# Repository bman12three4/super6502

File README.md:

# Super6502

## Overview

Super6502 is a microcomputer system powered by a 65C02 CPU. The goal of this
project is to create a computer system with modern features and the ability to
run modern software on an unmodified 65C02 core. While the project is almost
entirely contained in an FPGA, this rule is enforced by using an off the shelf
CPU.

## Goals

There are a few goals that I have for this project.

The number 1 goal is to create a pre-emptive multitasking operating system with
virtual memory.

I also have a few stretch goals:

1. Connect it to the internet

2. Boot linux (lol)

Along the way, there are a few milestones that I want to reach:

* USB support, including mass storage and peripherals
* HDMI Display output
* Ethernet

## Contributing

While I appreciate feedback, this my own personal project and I will not accept
external contributions.

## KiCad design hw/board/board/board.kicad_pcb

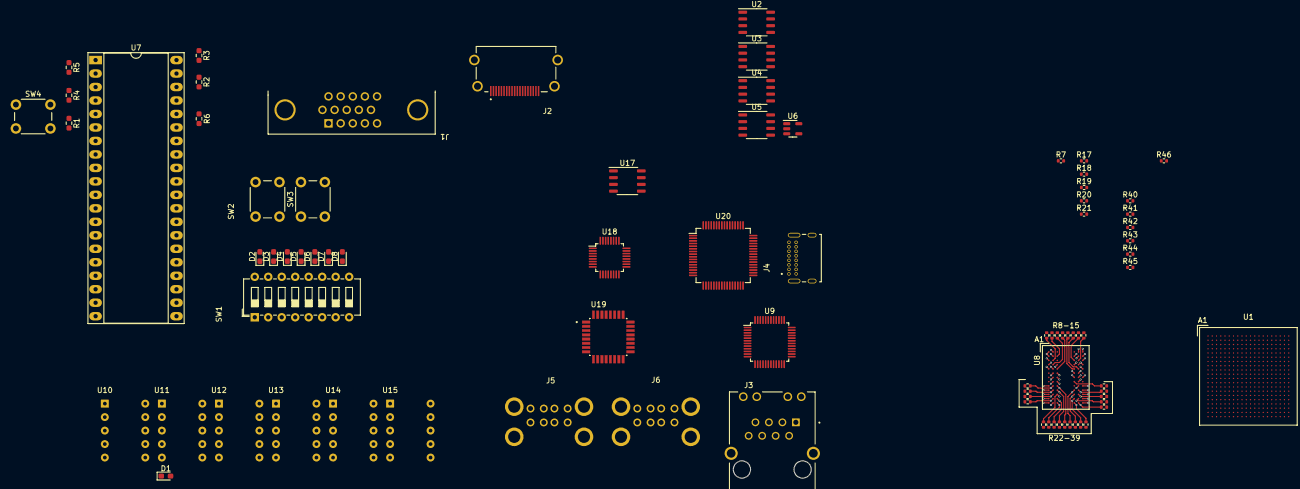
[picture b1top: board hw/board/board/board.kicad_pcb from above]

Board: 6 copper layers, 82 parts (0 on the bottom side), 59 nets.

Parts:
D1, D2, D3, D4, D5, D6, D7, D8: LED; LED_0603_1608Metric_Pad1.05x0.95mm_HandSolder
J1: DB15_Female_HighDensity_MountingHoles; ICD15S13E4GX00LF
J2: 10029449-111RLF; AMPHENOL_10029449-111RLF
J3: SI-50170-F; BEL_SI-50170-F
J4: USB4085-GF-A_REVB; GCT_USB4085-GF-A_REVB
J5, J6: USB_A_Stacked; 0672984091
R1, R2, R3, R4, R5, R6: 10K; R_0603_1608Metric_Pad0.98x0.95mm_HandSolder
R7: 100R; R_0402_1005Metric
R8, R9, R10, R11, R12, R13, R14, R15, R17, R18: 15R; R_0402_1005Metric
R19, R46: 240R; R_0402_1005Metric
R20, R21: 1k; R_0402_1005Metric
R22, R23, R24, R25, R26, R27, R28, R29, R30, R31, R32, R33, R34, R35, R36, R37, R38, R39, R40, R41, R42, R43, R44, R45: 40R; R_0402_1005Metric
SW1: SW_DIP_x08; SW_DIP_SPSTx08_Slide_6.7x21.88mm_W7.62mm_P2.54mm_LowProfile
SW2, SW3, SW4: SW_Push; SW_PUSH_6mm_H5mm
U1: BGA-400_17.0x17.0mm_Layout20x20_P0.8mm
U2, U3, U4, U5, U17: SOP-8_3.9x4.9mm_P1.27mm
U6: TSOT-23-5
U7: W65C02P; DIP-40_W15.24mm_Socket_LongPads
U8: BGA-78_8.0x10.5mm_Layout9x12_P0.8mm
U9: LQFP-48_7x7mm_P0.5mm
U10, U11, U12, U13, U14, U15: LTS-4802B
U18: MAX3421E; LQFP-32_5x5mm_P0.5mm
U19: TUSB2046BVFR; QFP80P900X900X160-32N
U20: FT4232H; LQFP-64_10x10mm_P0.5mm

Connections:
+1V35: R20.1, U1.L7 (VCCIO_DDR), U1.N7 (VCCIO_DDR), U1.P5 (VCCIO_DDR), U1.R2 (VCCIO_DDR), U1.R7 (VCCIO_DDR), U1.W4 (VCCIO_DDR), U8.A2 (VDD), U8.A9 (VDD), U8.B9 (VDDQ), U8.C1 (VDDQ), U8.D7 (VDD), U8.E2 (VDDQ), U8.E9 (VDDQ), U8.G2 (VDD), U8.G8 (VDD), U8.K1 (VDD), U8.K9 (VDD), U8.M1 (VDD), U8.M9 (VDD)
+3V3: R1.1, R2.1, R3.1, R4.1, R5.1, R6.1, U7.8 (VDD)
/cpu/CPU_BE: R6.2, U7.36 (BE)
/cpu/CPU_RDY: R5.2, U7.2 (RDY)
/cpu/~CPU_IRQB: R4.2, U7.4 (~IRQB)
/cpu/~CPU_NMIB: R1.2, SW4.2, U7.6 (~NMIB)
/cpu/~CPU_RESB: R3.2, U7.40 (~RESB)
/ddr/DDR_A0: R22.2, U1.U4 (DDR_A0), U8.K3 (A0)
/ddr/DDR_A1: R23.2, U1.W5 (DDR_A1), U8.L7 (A1)
/ddr/DDR_A2: R24.2, U1.V5 (DDR_A2), U8.L3 (A2)
/ddr/DDR_A3: R25.2, U1.T6 (DDR_A3), U8.K2 (A3)
/ddr/DDR_A4: R26.2, U1.T3 (DDR_A4), U8.L8 (A4)
/ddr/DDR_A5: R27.2, U1.T5 (DDR_A5), U8.L2 (A5)
/ddr/DDR_A6: R28.2, U1.T4 (DDR_A6), U8.M8 (A6)
/ddr/DDR_A7: R29.2, U1.T1 (DDR_A7), U8.M2 (A7)
/ddr/DDR_A8: R30.2, U1.R1 (DDR_A8), U8.N8 (A8)
/ddr/DDR_A9: R31.2, U1.T2 (DDR_A9), U8.M3 (A9)
/ddr/DDR_A10: R32.2, U1.R5 (DDR_A10), U8.H7 (A10/AP)
/ddr/DDR_A11: R33.2, U1.N5 (DDR_A11), U8.M7 (A11)
/ddr/DDR_A12: R34.2, U1.P4 (DDR_A12), U8.K7 (A12/BC#)
/ddr/DDR_A13: R35.2, U1.M6 (DDR_A13), U8.N3 (A13)
/ddr/DDR_A14: R36.2, U1.N4 (DDR_A14), U8.N7 (A14)
/ddr/DDR_BA0: R37.2, U1.K3 (DDR_BA0), U8.J2 (BA0)
/ddr/DDR_BA1: R38.2, U1.K2 (DDR_BA2), U8.K8 (BA1)
/ddr/DDR_BA2: R39.2, U1.K1 (DDR_BA2), U8.J3 (BA2)
/ddr/DDR_CAS#: R42.2, U1.P6 (DDR_CAS_N), U8.G3 (CAS#)
/ddr/DDR_CK: R7.1, U1.R3 (DDR_CK), U8.F7 (CK)
/ddr/DDR_CK#: R7.2, U1.R4 (DDR_CK_N), U8.G7 (CK#)
/ddr/DDR_CKE: R40.2, U1.N6 (DDR_CKE), U8.G9 (CKE)
/ddr/DDR_CS#: R44.2, U1.R6 (DDR_CS_N), U8.H2 (CS#)
/ddr/DDR_DM: R18.1, U1.W1 (DDR_DM0)
/ddr/DDR_DQ0: R8.1, U1.U3 (DDR_DQ0)
/ddr/DDR_DQ1: R9.1, U1.W3 (DDR_DQ1)
/ddr/DDR_DQ2: R10.1, U1.V3 (DDR_DQ2)
/ddr/DDR_DQ3: R11.1, U1.U2 (DDR_DQ3)
/ddr/DDR_DQ4: R12.1, U1.W2 (DDR_DQ4)
/ddr/DDR_DQ5: R13.1, U1.Y3 (DDR_DQ5)
/ddr/DDR_DQ6: R14.1, U1.Y4 (DDR_DQ6)
/ddr/DDR_DQ7: R15.1, U1.Y2 (DDR_DQ7)
/ddr/DDR_DQS#: R17.1, U1.U1 (DDR_DQS_N0)
/ddr/DDR_ODT: R45.2, U1.L6 (DDR_ODT), U8.G1 (ODT)
/ddr/DDR_RAS#: R43.2, U1.M4 (DDR_RAS_N), U8.F3 (RAS#)
/ddr/DDR_RESET#: U1.L4 (DDR_RST_N), U8.N2 (RESET#)
/ddr/DDR_WE#: R41.2, U1.K4 (DDR_WE_N), U8.H3 (WE#)
/ddr/VTT: R20.2, R21.1, R22.1, R23.1, R24.1, R25.1, R26.1, R27.1, R28.1, R29.1, R30.1, R31.1, R32.1, R33.1, R34.1, R35.1, R36.1, R37.1, R38.1, R39.1, R40.1, R41.1, R42.1, R43.1, R44.1, R45.1, U8.E1 (VREFDQ), U8.J8 (VREFCA)
GND: R19.2, R21.2, R46.2, SW4.1, U7.21 (VSS), U8.A1 (VSS), U8.A8 (VSS), U8.B1 (VSS), U8.B2 (VSSQ), U8.B8 (VSSQ), U8.C9 (VSSQ), U8.D1 (VSSQ), U8.D8 (VSS), U8.D9 (VSSQ), U8.F2 (VSS), U8.F8 (VSS), U8.J1 (VSS), U8.J9 (VSS), U8.L1 (VSS), U8.L9 (VSS), U8.N1 (VSS), U8.N9 (VSS)
unnamed: R46.1, U1.Y5 (DDR_ZQ)
unnamed: R2.2, U7.38 (~SOB)
unnamed: R18.2, U8.B7 (DM/TDQS)
unnamed: R8.2, U8.B3 (DQ0)
unnamed: R9.2, U8.C7 (DQ1)
unnamed: R10.2, U8.C2 (DQ2)
unnamed: R11.2, U8.C8 (DQ3)
unnamed: R12.2, U8.E3 (DQ4)
unnamed: R13.2, U8.E8 (DQ5)
unnamed: R14.2, U8.D2 (DQ6)
unnamed: R15.2, U8.E7 (DQ7)
unnamed: R17.2, U8.D3 (DQS#)
unnamed: R19.1, U8.H8 (ZQ)

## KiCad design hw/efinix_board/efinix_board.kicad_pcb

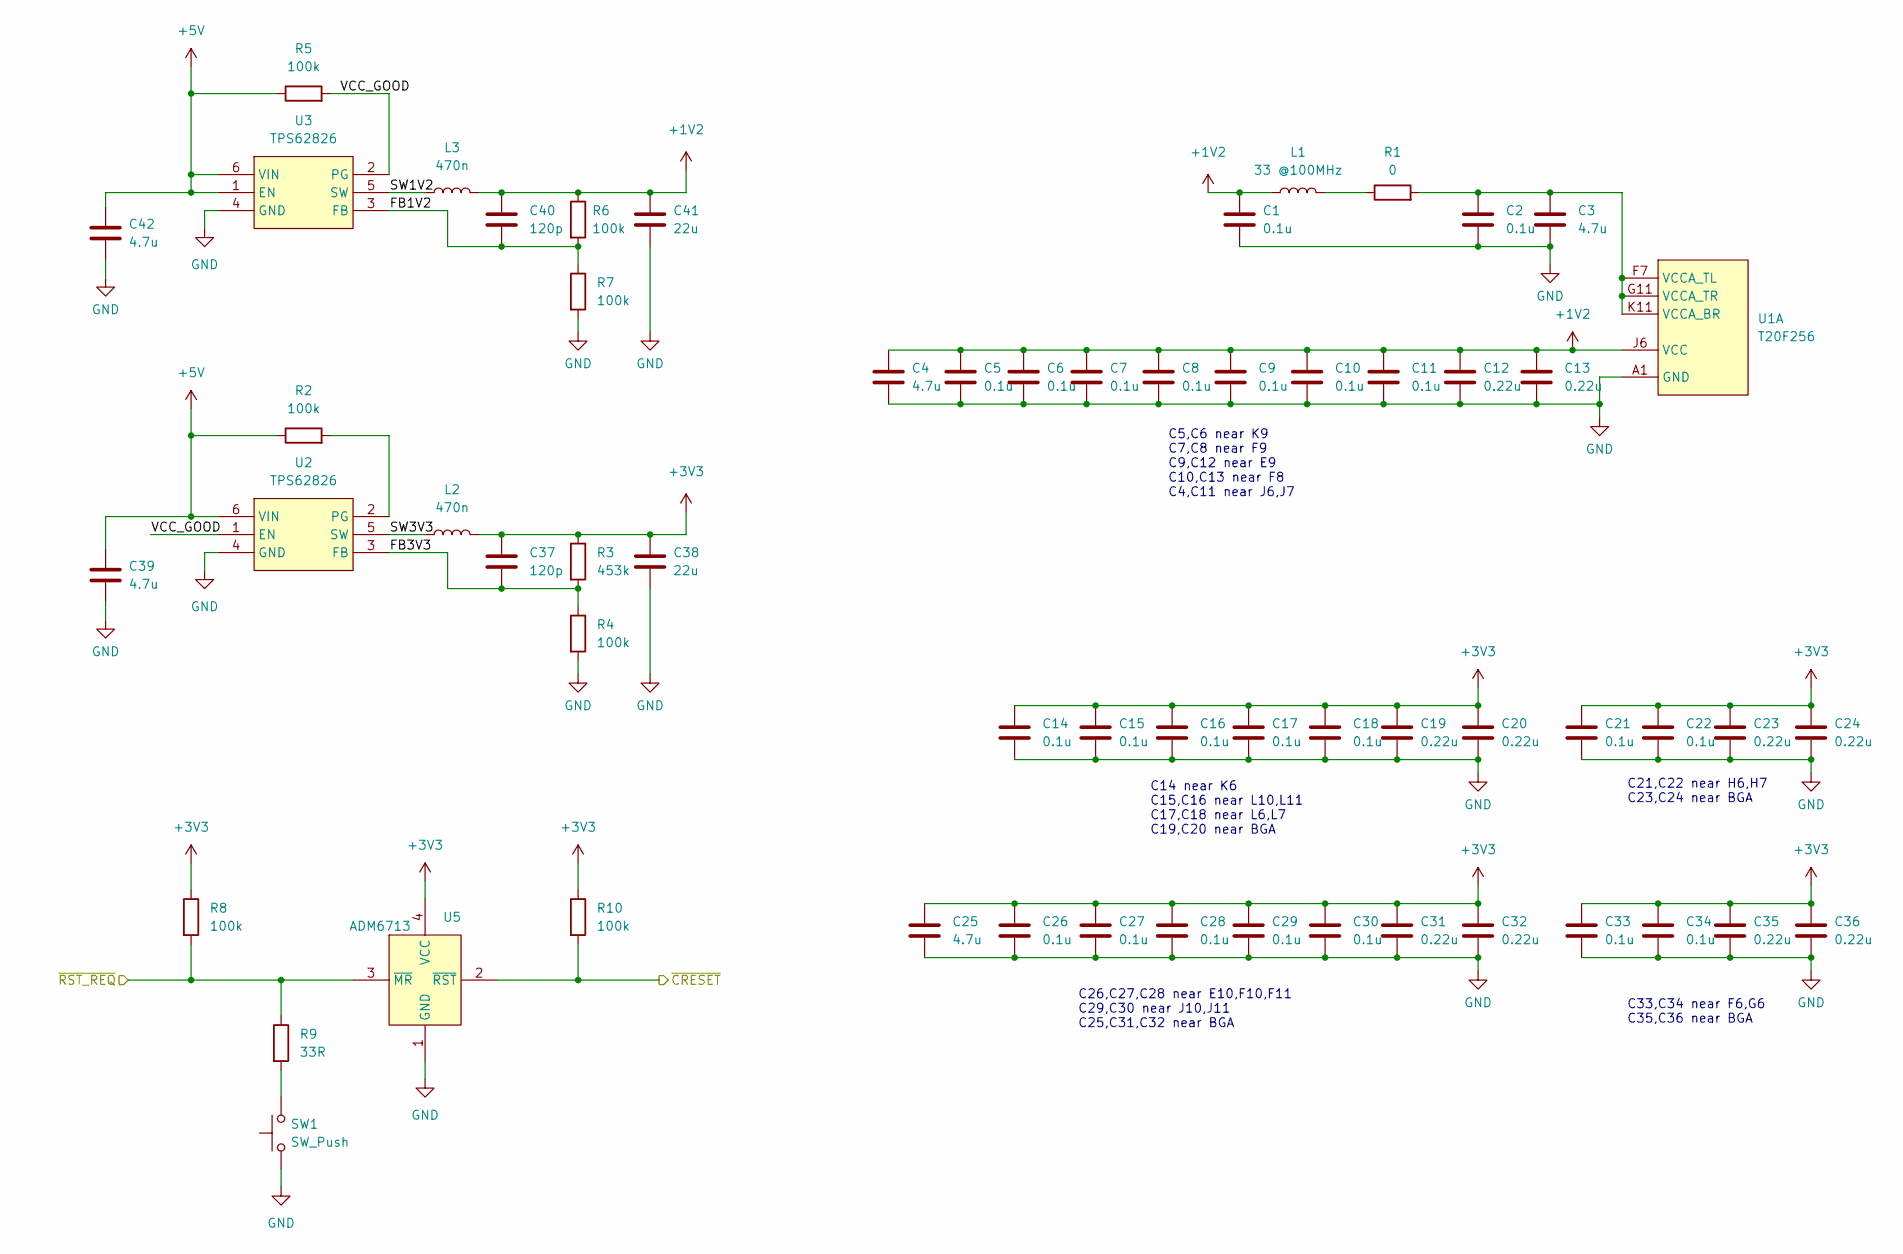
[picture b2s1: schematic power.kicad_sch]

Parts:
C1, C2, C5, C6, C7, C8, C9, C10, C11, C14, C15, C16, C17, C18, C21, C22, C26, C27, C28, C29, C30, C33, C34: 0.1u; C_0201_Small
C3, C4, C25: 4.7u; C_0402_1005Metric
C12, C13, C19, C20, C23, C24, C31, C32, C35, C36: 0.22u; C_0201_Small
C37, C40: 120p; C_0402_1005Metric
C38, C41: 22u; C_0603_1608Metric
C39, C42: 4.7u; C_0603_1608Metric
L1: 33 @100MHz; L_0402_1005Metric
L2, L3: 470n; L_Vishay_IHLP-1212
R1: 0; R_0603_1608Metric
R2, R5: 100k; R_0603_1608Metric
R3: 453k; R_0402_1005Metric
R4, R6, R7, R8, R10: 100k; R_0402_1005Metric
R9: 33R; R_0402_1005Metric
SW1: SW_Push; SW_1825966-1
U1: T20F256; BGA-256_14.0x14.0mm_Layout16x16_P0.8mm_Ball0.45mm_Pad0.32mm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
U2, U3: TPS62826; VFDFN-6
U5: ADM6713; ADM6711TAKSZ-REEL7

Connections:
+1V2: C1.1, C4.1, C5.1, C6.1, C7.1, C8.1, C9.1, C10.1, C11.1, C12.1, C13.1, C40.1, C41.1, L1.1, L3.2, R6.1, U1.E9 (VCC), U1.F8 (VCC), U1.F9 (VCC), U1.J6 (VCC), U1.J7 (VCC), U1.K9 (VCC)
+3V3: C14.1, C15.1, C16.1, C17.1, C18.1, C19.1, C20.1, C21.1, C22.1, C23.1, C24.1, C25.1, C26.1, C27.1, C28.1, C29.1, C30.1, C31.1, C32.1, C33.1, C34.1, C35.1, C36.1, C37.1, C38.1, L2.2, R3.1, R8.1, R10.1, U5.4 (VCC); also elsewhere on the board
+5V: C39.1, C42.1, R2.1, R5.1, U2.6 (VIN), U3.1 (EN), U3.6 (VIN)
/Power/FB1V2: C40.2, R6.2, R7.1, U3.3 (FB)
/Power/FB3V3: C37.2, R3.2, R4.1, U2.3 (FB)
/Power/SW1V2: L3.1, U3.5 (SW)
/Power/SW3V3: L2.1, U2.5 (SW)
/Power/VCC_GOOD: R5.2, U2.1 (EN), U3.2 (PG)
/Power/~CRESET: R10.2, U5.2 (~RST)
/Power/~RST_REQ: R8.2, R9.1, U5.3 (~MR)
GND: C1.2, C2.2, C3.2, C4.2, C5.2, C6.2, C7.2, C8.2, C9.2, C10.2, C11.2, C12.2, C13.2, C14.2, C15.2, C16.2, C17.2, C18.2, C19.2, C20.2, C21.2, C22.2, C23.2, C24.2, C25.2, C26.2, C27.2, C28.2, C29.2, C30.2, C31.2, C32.2, C33.2, C34.2, C35.2, C36.2, C38.2, C39.2, C41.2, C42.2, R4.2, R7.2, SW1.1, U1.A1 (GND), U1.A5 (GND), U1.A12 (GND), U1.A16 (GND), U1.D2 (GND), U1.D15 (GND), U1.G7 (GND), U1.G8 (GND), U1.G9 (GND), U1.G10 (GND), U1.H8 (GND), U1.H9 (GND), U1.H10 (GND), U1.H11 (GND), U1.J1 (GND), U1.J8 (GND), U1.J9 (GND), U1.J16 (GND), U1.K7 (GND), U1.K8 (GND), U1.K10 (GND), U1.L8 (GND), U1.L9 (GND), U1.N2 (GND), U1.N15 (GND), U1.R7 (GND), U1.R10 (GND), U1.T1 (GND), U1.T4 (GND), U1.T13 (GND), U1.T16 (GND), U2.4 (GND), U3.4 (GND), U5.1 (GND); also elsewhere on the board
unnamed: C2.1, C3.1, R1.2, U1.F7 (VCCA_TL), U1.G11 (VCCA_TR), U1.K11 (VCCA_BR)
unnamed: L1.2, R1.1
unnamed: R2.2, U2.2 (PG)
unnamed: R9.2, SW1.2

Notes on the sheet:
C21,C22 near H6,H7 C23,C24 near BGA
C5,C6 near K9 C7,C8 near F9 C9,C12 near E9 C10,C13 near F8 C4,C11 near J6,J7
C33,C34 near F6,G6 C35,C36 near BGA
C26,C27,C28 near E10,F10,F11 C29,C30 near J10,J11 C25,C31,C32 near BGA
C14 near K6 C15,C16 near L10,L11 C17,C18 near L6,L7 C19,C20 near BGA

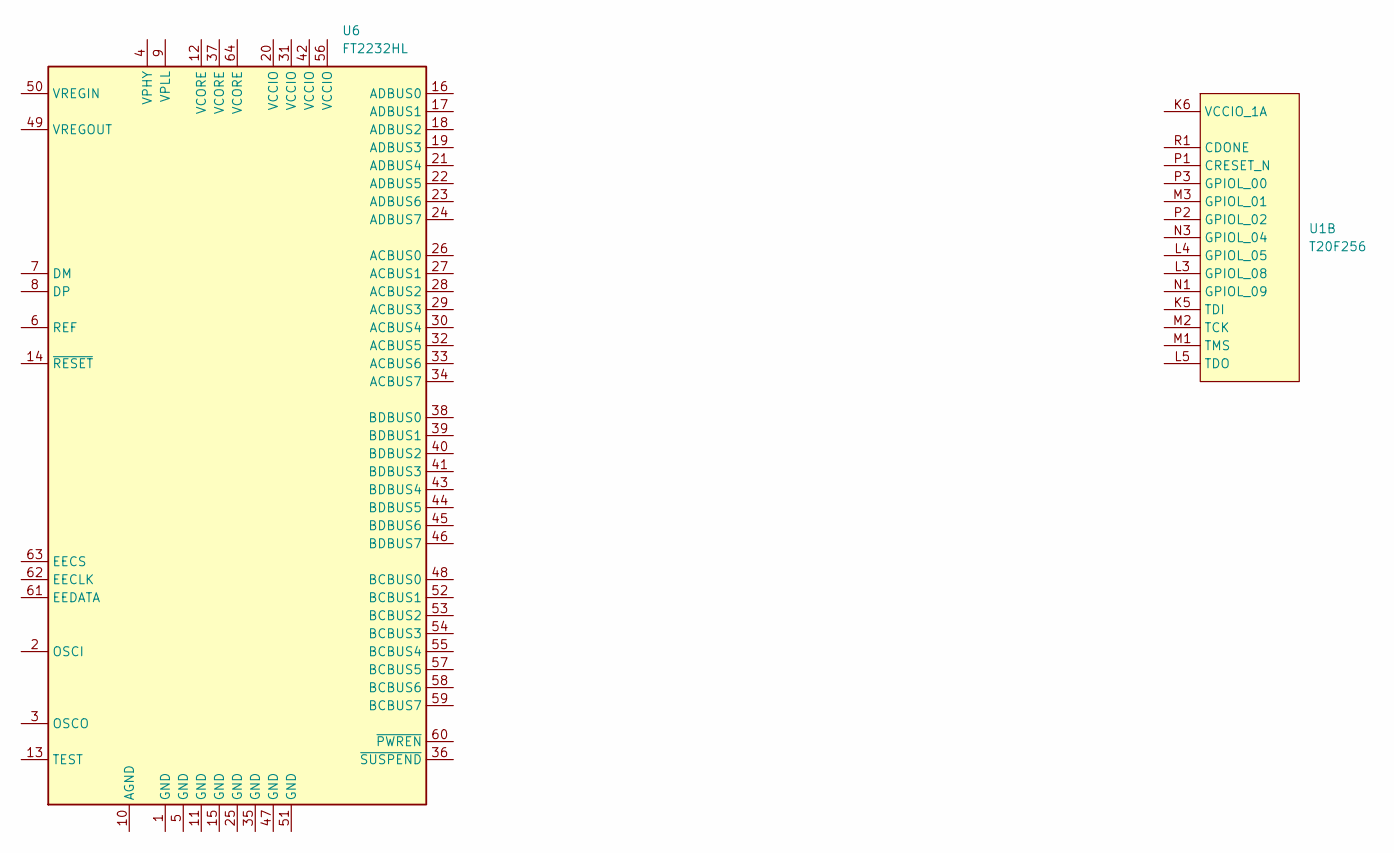
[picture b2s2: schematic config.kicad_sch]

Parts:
U1: T20F256; BGA-256_14.0x14.0mm_Layout16x16_P0.8mm_Ball0.45mm_Pad0.32mm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
U6: FT2232HL; LQFP-64_10x10mm_P0.5mm

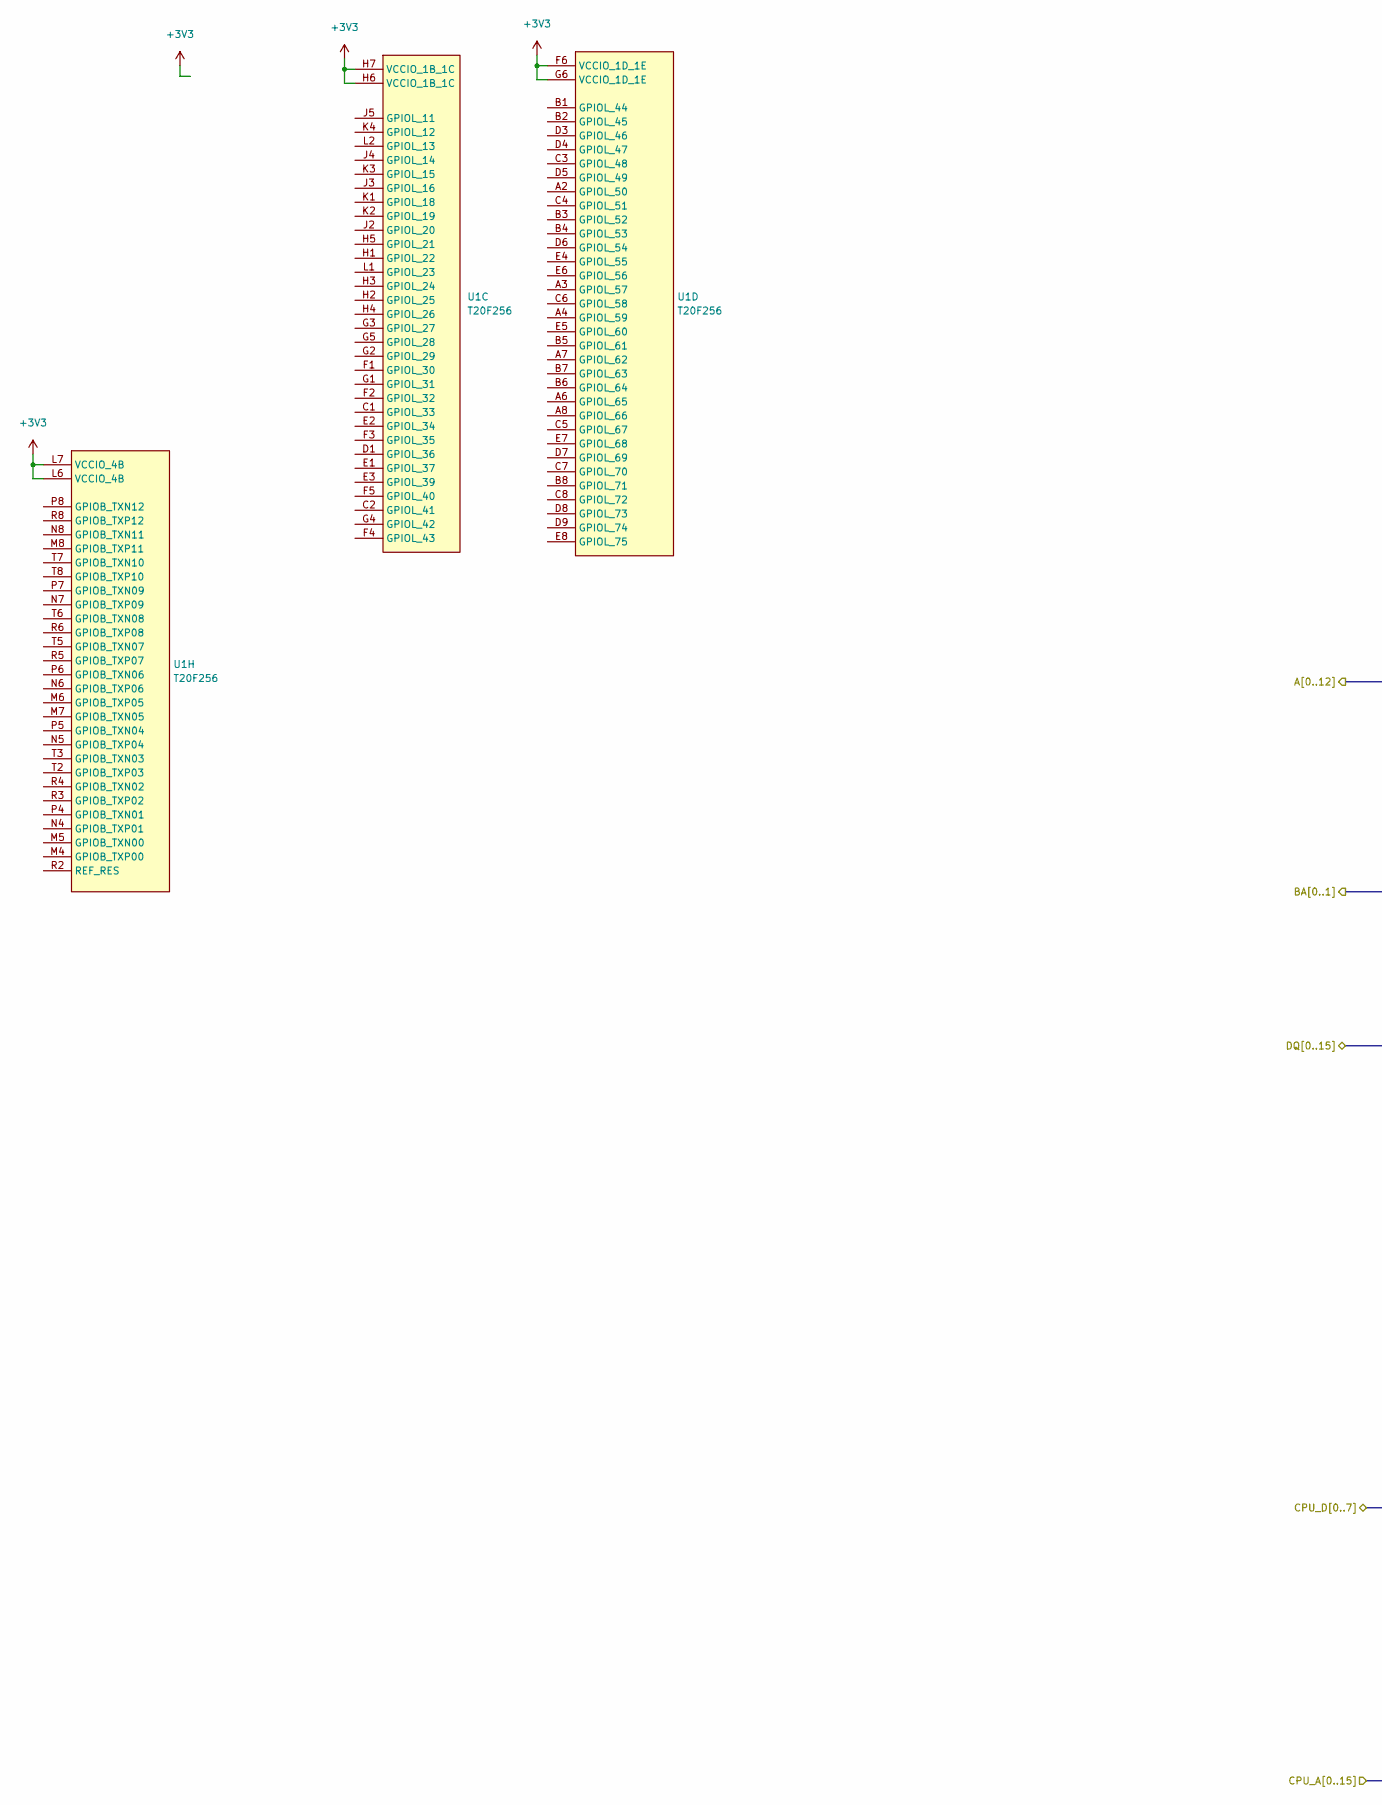
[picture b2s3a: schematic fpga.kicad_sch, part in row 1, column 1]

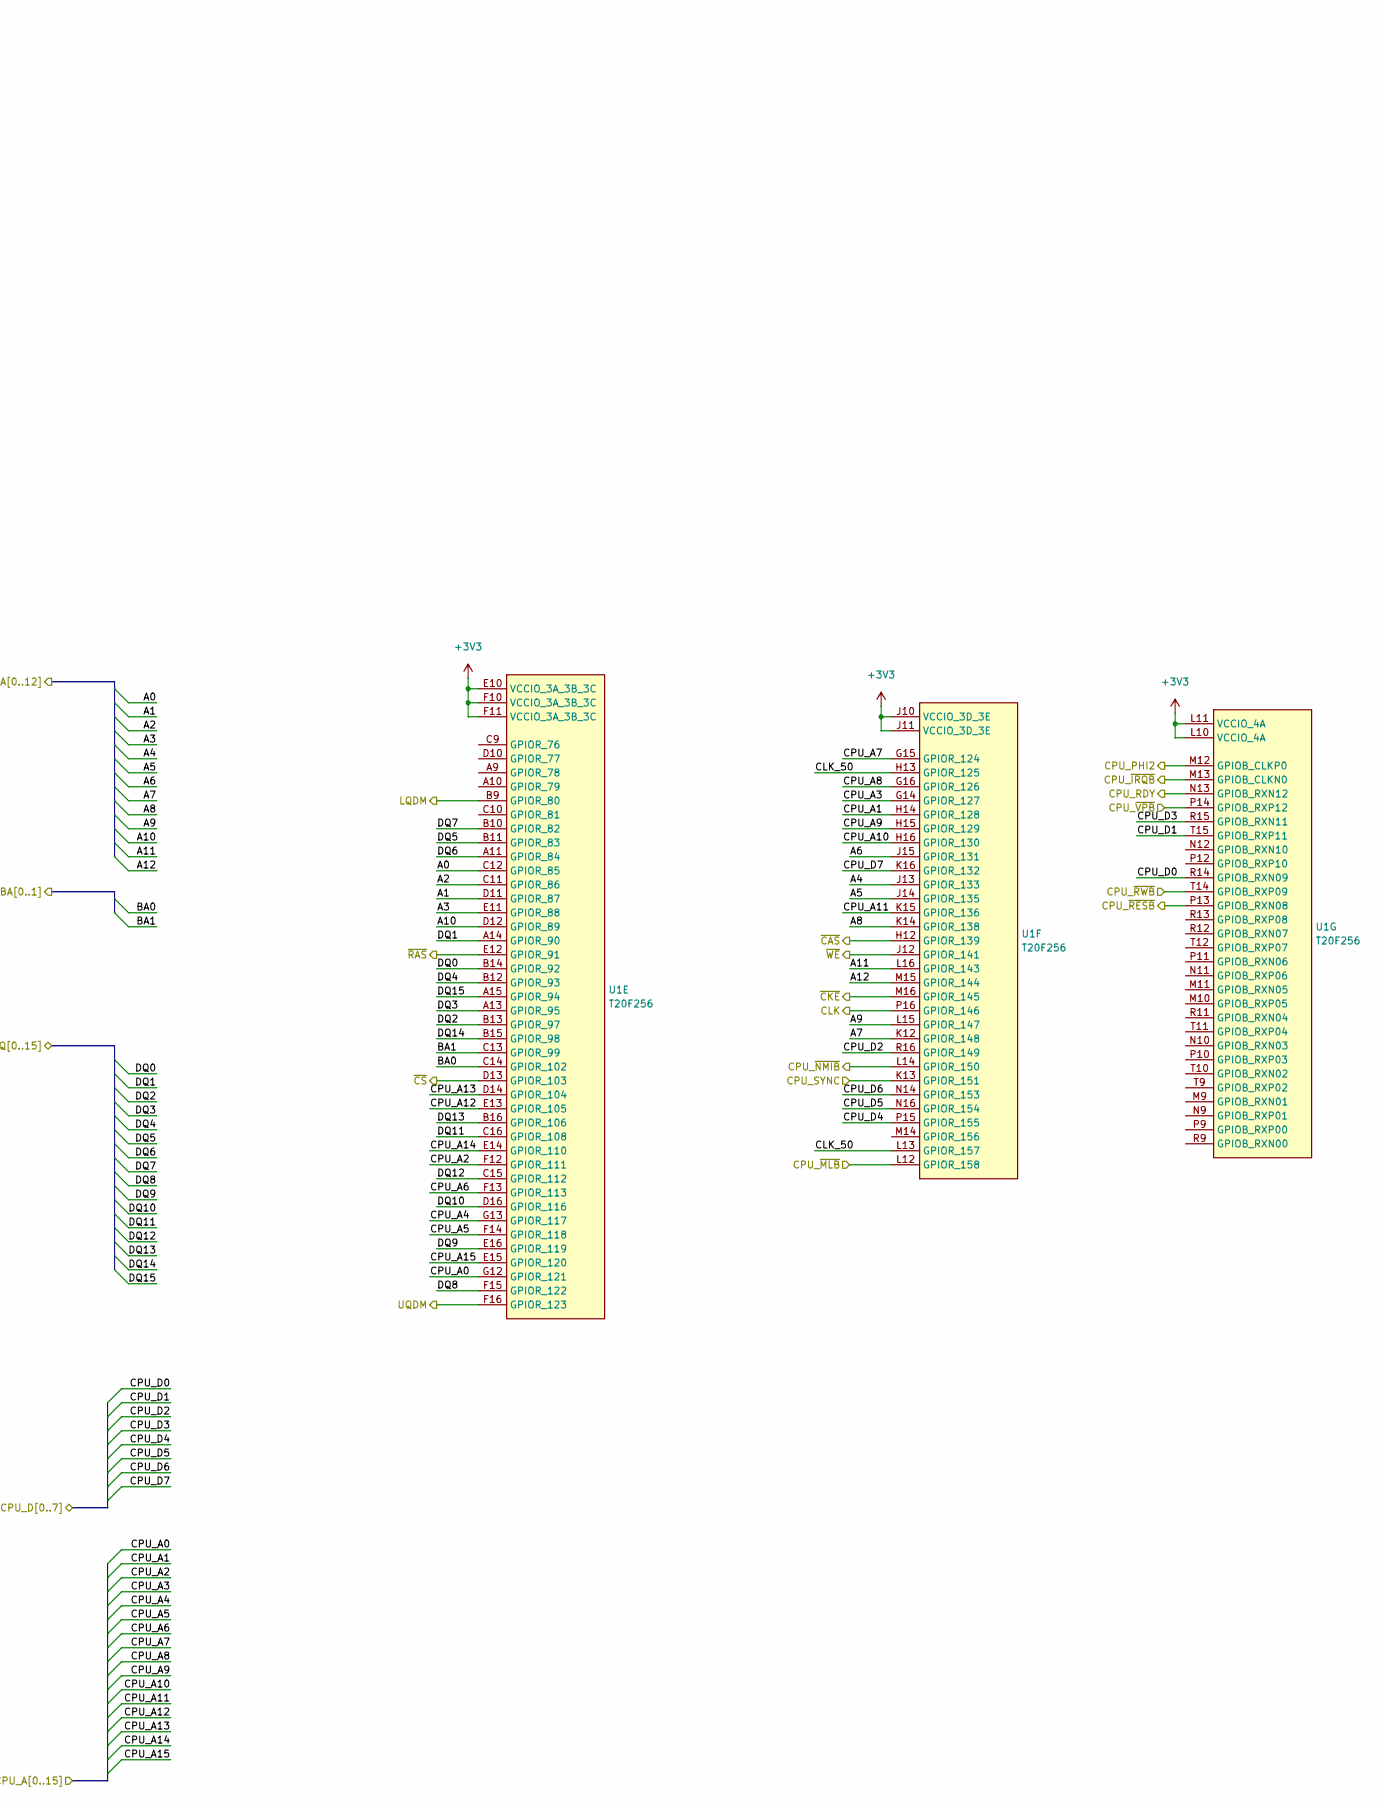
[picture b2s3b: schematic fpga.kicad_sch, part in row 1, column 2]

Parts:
U1: T20F256; BGA-256_14.0x14.0mm_Layout16x16_P0.8mm_Ball0.45mm_Pad0.32mm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

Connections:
+3V3: U1.E10 (VCCIO_3A_3B_3C), U1.F6 (VCCIO_1D_1E), U1.F10 (VCCIO_3A_3B_3C), U1.F11 (VCCIO_3A_3B_3C), U1.G6 (VCCIO_1D_1E), U1.H6 (VCCIO_1B_1C), U1.H7 (VCCIO_1B_1C), U1.J10 (VCCIO_3D_3E), U1.J11 (VCCIO_3D_3E), U1.L6 (VCCIO_4B), U1.L7 (VCCIO_4B), U1.L10 (VCCIO_4A), U1.L11 (VCCIO_4A); also elsewhere on the board
/cpu/CPU_A0: U1.G12 (GPIOR_121); also elsewhere on the board
/cpu/CPU_A1: U1.H14 (GPIOR_128); also elsewhere on the board
/cpu/CPU_A2: U1.F12 (GPIOR_111); also elsewhere on the board
/cpu/CPU_A3: U1.G14 (GPIOR_127); also elsewhere on the board
/cpu/CPU_A4: U1.G13 (GPIOR_117); also elsewhere on the board
/cpu/CPU_A5: U1.F14 (GPIOR_118); also elsewhere on the board
/cpu/CPU_A6: U1.F13 (GPIOR_113); also elsewhere on the board
/cpu/CPU_A7: U1.G15 (GPIOR_124); also elsewhere on the board
/cpu/CPU_A8: U1.G16 (GPIOR_126); also elsewhere on the board
/cpu/CPU_A9: U1.H15 (GPIOR_129); also elsewhere on the board
/cpu/CPU_A10: U1.H16 (GPIOR_130); also elsewhere on the board
/cpu/CPU_A11: U1.K15 (GPIOR_136); also elsewhere on the board
/cpu/CPU_A12: U1.E13 (GPIOR_105); also elsewhere on the board
/cpu/CPU_A13: U1.D14 (GPIOR_104); also elsewhere on the board
/cpu/CPU_A14: U1.E14 (GPIOR_110); also elsewhere on the board
/cpu/CPU_A15: U1.E15 (GPIOR_120); also elsewhere on the board
/cpu/CPU_D0: U1.R14 (GPIOB_RXN09); also elsewhere on the board
/cpu/CPU_D1: U1.T15 (GPIOB_RXP11); also elsewhere on the board
/cpu/CPU_D2: U1.R16 (GPIOR_149); also elsewhere on the board
/cpu/CPU_D3: U1.R15 (GPIOB_RXN11); also elsewhere on the board
/cpu/CPU_D4: U1.P15 (GPIOR_155); also elsewhere on the board
/cpu/CPU_D5: U1.N16 (GPIOR_154); also elsewhere on the board
/cpu/CPU_D6: U1.N14 (GPIOR_153); also elsewhere on the board
/cpu/CPU_D7: U1.K16 (GPIOR_132); also elsewhere on the board
/cpu/CPU_PHI2: U1.M12 (GPIOB_CLKP0); also elsewhere on the board
/cpu/CPU_RDY: U1.N13 (GPIOB_RXN12); also elsewhere on the board
/cpu/CPU_SYNC: U1.K13 (GPIOR_151); also elsewhere on the board
/cpu/CPU_~IRQB: U1.M13 (GPIOB_CLKN0); also elsewhere on the board
/cpu/CPU_~MLB: U1.L12 (GPIOR_158); also elsewhere on the board
/cpu/CPU_~NMIB: U1.L14 (GPIOR_150); also elsewhere on the board
/cpu/CPU_~RESB: U1.P13 (GPIOB_RXN08); also elsewhere on the board
/cpu/CPU_~RWB: U1.T14 (GPIOB_RXP09); also elsewhere on the board
/cpu/CPU_~VPB: U1.P14 (GPIOB_RXP12); also elsewhere on the board
/fpga/A0: U1.C12 (GPIOR_85); also elsewhere on the board
/fpga/A1: U1.D11 (GPIOR_87); also elsewhere on the board
/fpga/A2: U1.C11 (GPIOR_86); also elsewhere on the board
/fpga/A3: U1.E11 (GPIOR_88); also elsewhere on the board
/fpga/A4: U1.J13 (GPIOR_133); also elsewhere on the board
/fpga/A5: U1.J14 (GPIOR_135); also elsewhere on the board
/fpga/A6: U1.J15 (GPIOR_131); also elsewhere on the board
/fpga/A7: U1.K12 (GPIOR_148); also elsewhere on the board
/fpga/A8: U1.K14 (GPIOR_138); also elsewhere on the board
/fpga/A9: U1.L15 (GPIOR_147); also elsewhere on the board
/fpga/A10: U1.D12 (GPIOR_89); also elsewhere on the board
/fpga/A11: U1.L16 (GPIOR_143); also elsewhere on the board
/fpga/A12: U1.M15 (GPIOR_144); also elsewhere on the board
/fpga/BA0: U1.C14 (GPIOR_102); also elsewhere on the board
/fpga/BA1: U1.C13 (GPIOR_99); also elsewhere on the board
/fpga/CLK: U1.P16 (GPIOR_146); also elsewhere on the board
/fpga/CLK_50: U1.H13 (GPIOR_125), U1.L13 (GPIOR_157)
/fpga/DQ0: U1.B14 (GPIOR_92); also elsewhere on the board
/fpga/DQ1: U1.A14 (GPIOR_90); also elsewhere on the board
/fpga/DQ2: U1.B13 (GPIOR_97); also elsewhere on the board
/fpga/DQ3: U1.A13 (GPIOR_95); also elsewhere on the board
/fpga/DQ4: U1.B12 (GPIOR_93); also elsewhere on the board
/fpga/DQ5: U1.B11 (GPIOR_83); also elsewhere on the board
/fpga/DQ6: U1.A11 (GPIOR_84); also elsewhere on the board
/fpga/DQ7: U1.B10 (GPIOR_82); also elsewhere on the board
/fpga/DQ8: U1.F15 (GPIOR_122); also elsewhere on the board
/fpga/DQ9: U1.E16 (GPIOR_119); also elsewhere on the board
/fpga/DQ10: U1.D16 (GPIOR_116); also elsewhere on the board
/fpga/DQ11: U1.C16 (GPIOR_108); also elsewhere on the board
/fpga/DQ12: U1.C15 (GPIOR_112); also elsewhere on the board
/fpga/DQ13: U1.B16 (GPIOR_106); also elsewhere on the board
/fpga/DQ14: U1.B15 (GPIOR_98); also elsewhere on the board
/fpga/DQ15: U1.A15 (GPIOR_94); also elsewhere on the board
/fpga/LQDM: U1.B9 (GPIOR_80); also elsewhere on the board
/fpga/UQDM: U1.F16 (GPIOR_123); also elsewhere on the board
/fpga/~CAS: U1.H12 (GPIOR_139); also elsewhere on the board
/fpga/~CKE: U1.M16 (GPIOR_145); also elsewhere on the board
/fpga/~CS: U1.D13 (GPIOR_103); also elsewhere on the board
/fpga/~RAS: U1.E12 (GPIOR_91); also elsewhere on the board
/fpga/~WE: U1.J12 (GPIOR_141); also elsewhere on the board

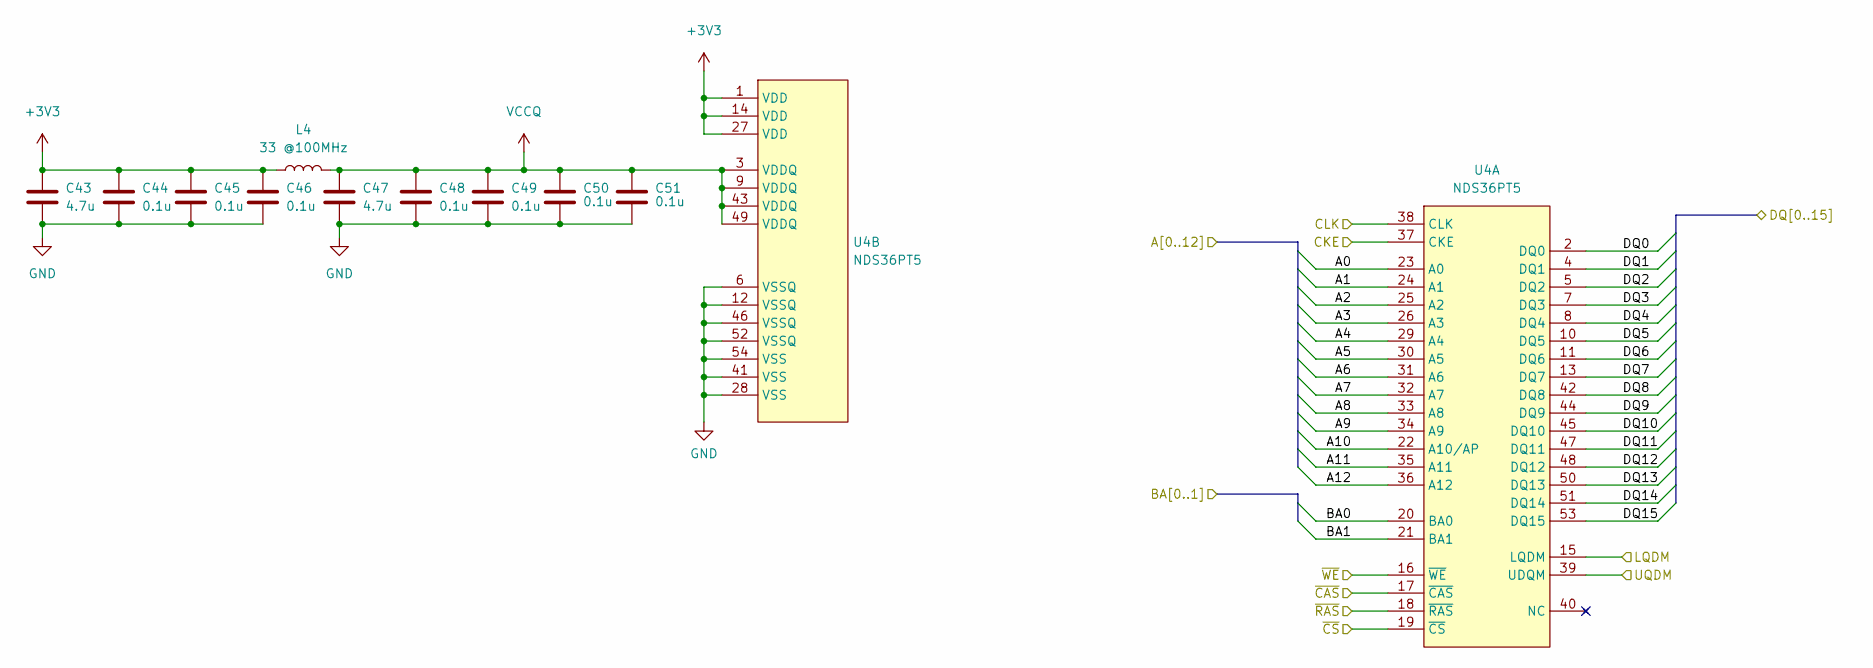
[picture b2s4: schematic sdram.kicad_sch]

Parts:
C43, C47: 4.7u; C_0402_1005Metric
C44, C45, C46, C48, C49, C50, C51: 0.1u; C_0201_Small
L4: 33 @100MHz; L_0402_1005Metric
U4: NDS36PT5; TSOP-II-54_22.2x10.16mm_P0.8mm

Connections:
+3V3: C43.1, C44.1, C45.1, C46.1, L4.1, U4.1 (VDD), U4.14 (VDD), U4.27 (VDD); also elsewhere on the board
/fpga/A0: U4.23 (A0); also elsewhere on the board
/fpga/A1: U4.24 (A1); also elsewhere on the board
/fpga/A2: U4.25 (A2); also elsewhere on the board
/fpga/A3: U4.26 (A3); also elsewhere on the board
/fpga/A4: U4.29 (A4); also elsewhere on the board
/fpga/A5: U4.30 (A5); also elsewhere on the board
/fpga/A6: U4.31 (A6); also elsewhere on the board
/fpga/A7: U4.32 (A7); also elsewhere on the board
/fpga/A8: U4.33 (A8); also elsewhere on the board
/fpga/A9: U4.34 (A9); also elsewhere on the board
/fpga/A10: U4.22 (A10/AP); also elsewhere on the board
/fpga/A11: U4.35 (A11); also elsewhere on the board
/fpga/A12: U4.36 (A12); also elsewhere on the board
/fpga/BA0: U4.20 (BA0); also elsewhere on the board
/fpga/BA1: U4.21 (BA1); also elsewhere on the board
/fpga/CLK: U4.38 (CLK); also elsewhere on the board
/fpga/DQ0: U4.2 (DQ0); also elsewhere on the board
/fpga/DQ1: U4.4 (DQ1); also elsewhere on the board
/fpga/DQ2: U4.5 (DQ2); also elsewhere on the board
/fpga/DQ3: U4.7 (DQ3); also elsewhere on the board
/fpga/DQ4: U4.8 (DQ4); also elsewhere on the board
/fpga/DQ5: U4.10 (DQ5); also elsewhere on the board
/fpga/DQ6: U4.11 (DQ6); also elsewhere on the board
/fpga/DQ7: U4.13 (DQ7); also elsewhere on the board
/fpga/DQ8: U4.42 (DQ8); also elsewhere on the board
/fpga/DQ9: U4.44 (DQ9); also elsewhere on the board
/fpga/DQ10: U4.45 (DQ10); also elsewhere on the board
/fpga/DQ11: U4.47 (DQ11); also elsewhere on the board
/fpga/DQ12: U4.48 (DQ12); also elsewhere on the board
/fpga/DQ13: U4.50 (DQ13); also elsewhere on the board
/fpga/DQ14: U4.51 (DQ14); also elsewhere on the board
/fpga/DQ15: U4.53 (DQ15); also elsewhere on the board
/fpga/LQDM: U4.15 (LQDM); also elsewhere on the board
/fpga/UQDM: U4.39 (UDQM); also elsewhere on the board
/fpga/~CAS: U4.17 (~CAS); also elsewhere on the board
/fpga/~CKE: U4.37 (CKE); also elsewhere on the board
/fpga/~CS: U4.19 (~CS); also elsewhere on the board
/fpga/~RAS: U4.18 (~RAS); also elsewhere on the board
/fpga/~WE: U4.16 (~WE); also elsewhere on the board
GND: C43.2, C44.2, C45.2, C46.2, C47.2, C48.2, C49.2, C50.2, C51.2, U4.6 (VSSQ), U4.12 (VSSQ), U4.28 (VSS), U4.41 (VSS), U4.46 (VSSQ), U4.52 (VSSQ), U4.54 (VSS); also elsewhere on the board
VCCQ: C47.1, C48.1, C49.1, C50.1, C51.1, L4.2, U4.3 (VDDQ), U4.9 (VDDQ), U4.43 (VDDQ), U4.49 (VDDQ)

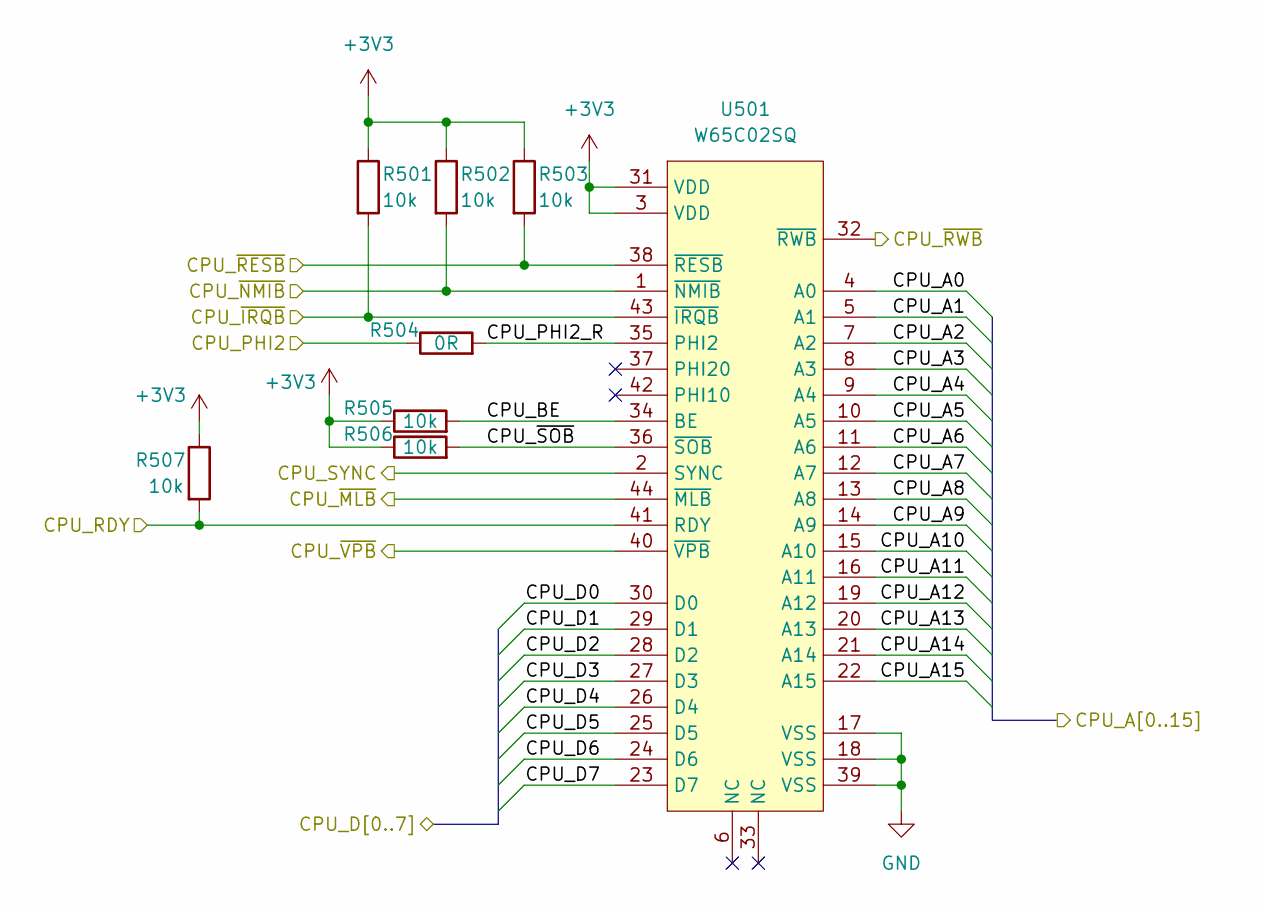
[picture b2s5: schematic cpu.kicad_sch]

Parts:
R501, R502, R503, R505, R506, R507: 10k; R_0402_1005Metric
R504: 0R; R_0402_1005Metric
U501: W65C02SQ; LQFP-44_10x10mm_P0.8mm

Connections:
+3V3: R501.1, R502.1, R503.1, R505.1, R506.1, R507.1, U501.3 (VDD), U501.31 (VDD); also elsewhere on the board
/cpu/CPU_A0: U501.4 (A0); also elsewhere on the board
/cpu/CPU_A1: U501.5 (A1); also elsewhere on the board
/cpu/CPU_A2: U501.7 (A2); also elsewhere on the board
/cpu/CPU_A3: U501.8 (A3); also elsewhere on the board
/cpu/CPU_A4: U501.9 (A4); also elsewhere on the board
/cpu/CPU_A5: U501.10 (A5); also elsewhere on the board
/cpu/CPU_A6: U501.11 (A6); also elsewhere on the board
/cpu/CPU_A7: U501.12 (A7); also elsewhere on the board
/cpu/CPU_A8: U501.13 (A8); also elsewhere on the board
/cpu/CPU_A9: U501.14 (A9); also elsewhere on the board
/cpu/CPU_A10: U501.15 (A10); also elsewhere on the board
/cpu/CPU_A11: U501.16 (A11); also elsewhere on the board
/cpu/CPU_A12: U501.19 (A12); also elsewhere on the board
/cpu/CPU_A13: U501.20 (A13); also elsewhere on the board
/cpu/CPU_A14: U501.21 (A14); also elsewhere on the board
/cpu/CPU_A15: U501.22 (A15); also elsewhere on the board
/cpu/CPU_BE: R505.2, U501.34 (BE)
/cpu/CPU_D0: U501.30 (D0); also elsewhere on the board
/cpu/CPU_D1: U501.29 (D1); also elsewhere on the board
/cpu/CPU_D2: U501.28 (D2); also elsewhere on the board
/cpu/CPU_D3: U501.27 (D3); also elsewhere on the board
/cpu/CPU_D4: U501.26 (D4); also elsewhere on the board
/cpu/CPU_D5: U501.25 (D5); also elsewhere on the board
/cpu/CPU_D6: U501.24 (D6); also elsewhere on the board
/cpu/CPU_D7: U501.23 (D7); also elsewhere on the board
/cpu/CPU_PHI2: R504.1; also elsewhere on the board
/cpu/CPU_PHI2_R: R504.2, U501.35 (PHI2)
/cpu/CPU_RDY: R507.2, U501.41 (RDY); also elsewhere on the board
/cpu/CPU_SYNC: U501.2 (SYNC); also elsewhere on the board
/cpu/CPU_~IRQB: R501.2, U501.43 (~IRQB); also elsewhere on the board
/cpu/CPU_~MLB: U501.44 (~MLB); also elsewhere on the board
/cpu/CPU_~NMIB: R502.2, U501.1 (~NMIB); also elsewhere on the board
/cpu/CPU_~RESB: R503.2, U501.38 (~RESB); also elsewhere on the board
/cpu/CPU_~RWB: U501.32 (~RWB); also elsewhere on the board
/cpu/CPU_~SOB: R506.2, U501.36 (~SOB)
/cpu/CPU_~VPB: U501.40 (~VPB); also elsewhere on the board
GND: U501.17 (VSS), U501.18 (VSS), U501.39 (VSS); also elsewhere on the board

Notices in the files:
hw/fpga/super6502.qsf:
Copyright (C) 2018  Intel Corporation. All rights reserved.
parts and their libraries:
Copyright 2021 Accelerated Designs. All rights reserved.
